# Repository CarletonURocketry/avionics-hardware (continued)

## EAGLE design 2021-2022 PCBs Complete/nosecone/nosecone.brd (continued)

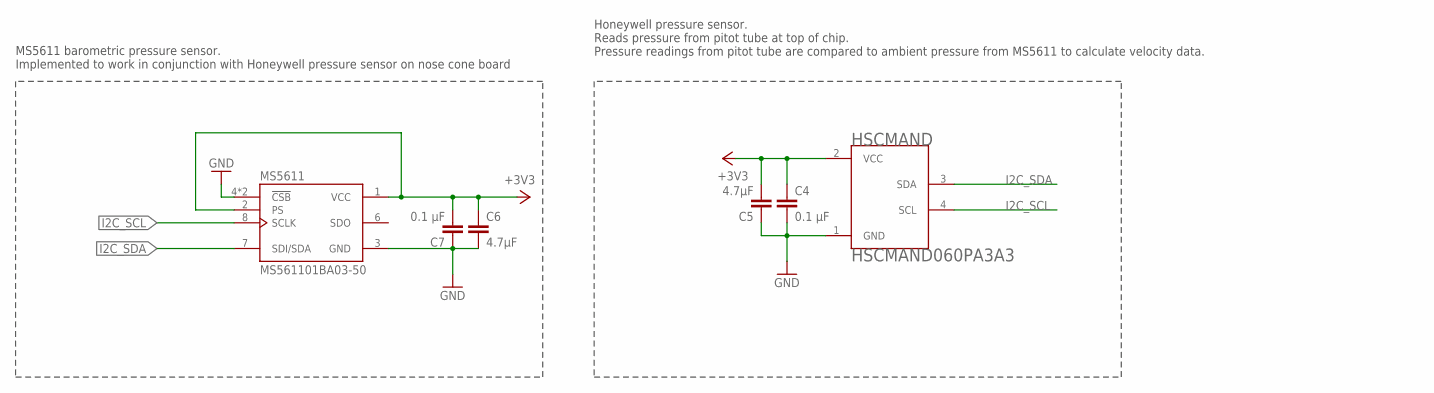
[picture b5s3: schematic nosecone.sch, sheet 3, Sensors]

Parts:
C4, C7: 0.1 µF; C0805
C5, C6: 4.7µF; C0805
HSCMAND: HSCMAND060PA3A3; HSC-SMT
MS5611: MS561101BA03-50; SON125P500X300X100-8N

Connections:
+3V3: C4.1, C5.2, C6.1, C7.2, HSCMAND.2 (VCC), MS5611.1 (VCC), MS5611.2 (PS); also elsewhere on the board
GND: C4.2, C5.1, C6.2, C7.1, HSCMAND.1 (GND), MS5611.3 (GND), MS5611.4 (!CSB), MS5611.5 (!CSB); also elsewhere on the board
I2C_SCL: HSCMAND.4 (SCL), MS5611.8 (SCLK); also elsewhere on the board
I2C_SDA: HSCMAND.3 (SDA), MS5611.7 (SDI/SDA); also elsewhere on the board

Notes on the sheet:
MS5611 barometric pressure sensor. Implemented to work in conjunction with Honeywell pressure sensor on nose cone board
Honeywell pressure sensor. Reads pressure from pitot tube at top of chip. Pressure readings from pitot tube are compared to ambient pressure from MS5611 to calculate velocity data.

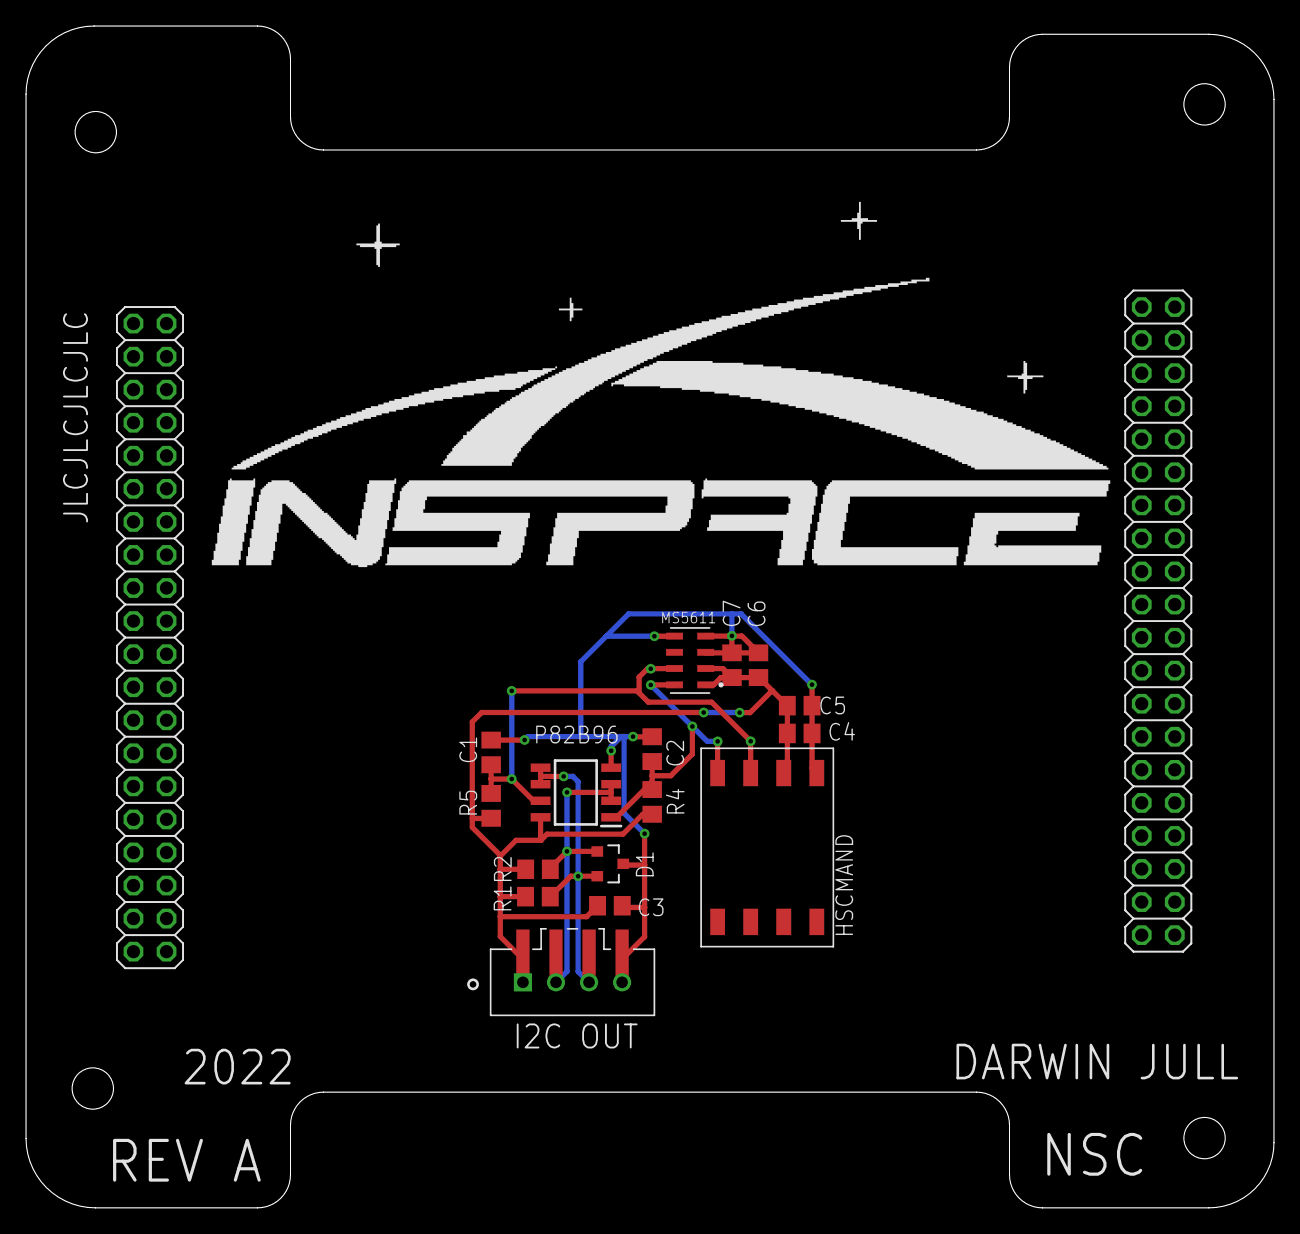
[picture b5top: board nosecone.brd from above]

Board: 2 copper layers, 95.9 x 90.8 mm, 19 parts (0 on the bottom side), 8 nets.

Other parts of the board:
U$2: INSPACE_7CM

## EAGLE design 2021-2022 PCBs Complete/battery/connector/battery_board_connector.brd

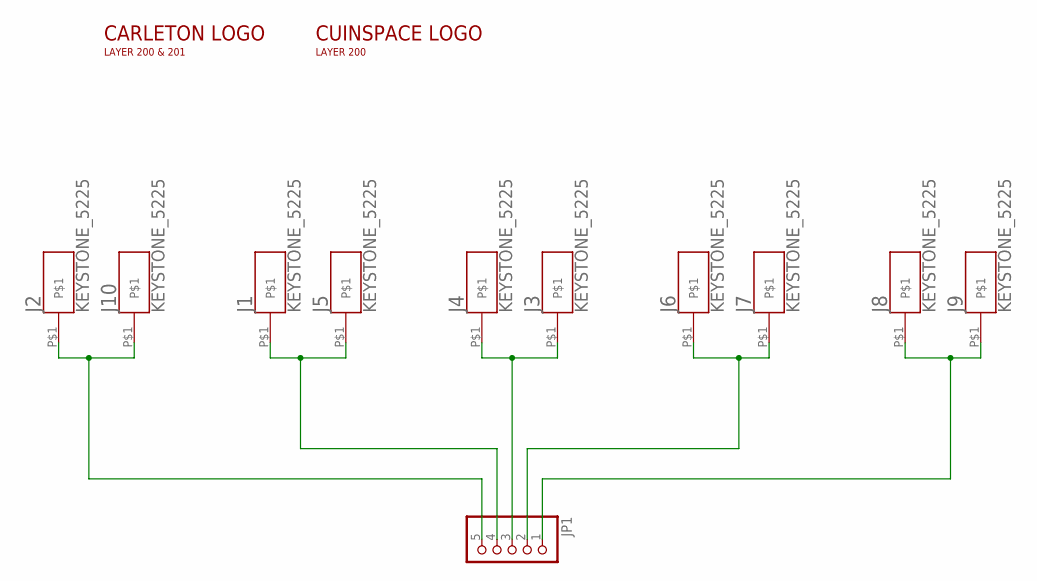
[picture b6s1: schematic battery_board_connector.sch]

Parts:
J1, J2, J3, J4, J5, J6, J7, J8, J9, J10: KEYSTONE_5225
JP1: PINHD-1X5; 1X05
U$1: INSPACE3CM; INSPACE_3CM
U$2: CARLETON3CM; CARLETONU_3CM

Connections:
unnamed: J2.P$1, J10.P$1, JP1.5
unnamed: J1.P$1, J5.P$1, JP1.4
unnamed: J3.P$1, J4.P$1, JP1.3
unnamed: J6.P$1, J7.P$1, JP1.2
unnamed: J8.P$1, J9.P$1, JP1.1

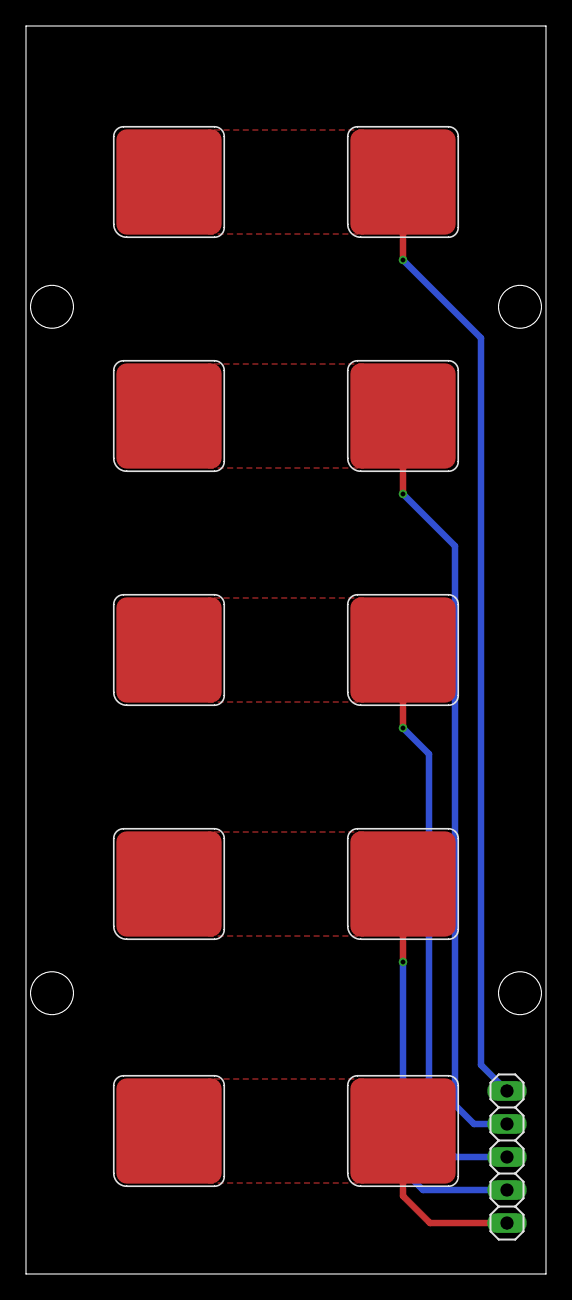
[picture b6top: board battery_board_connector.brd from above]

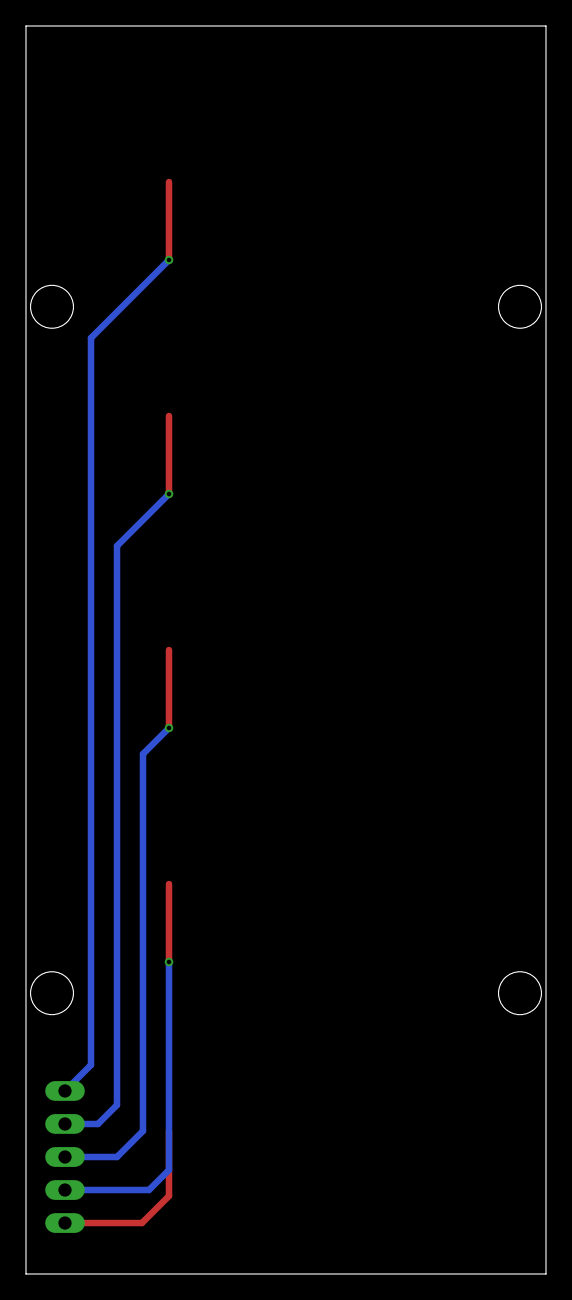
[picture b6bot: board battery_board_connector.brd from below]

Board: 2 copper layers, 40.0 x 96.0 mm, 13 parts (2 on the bottom side), 5 nets.

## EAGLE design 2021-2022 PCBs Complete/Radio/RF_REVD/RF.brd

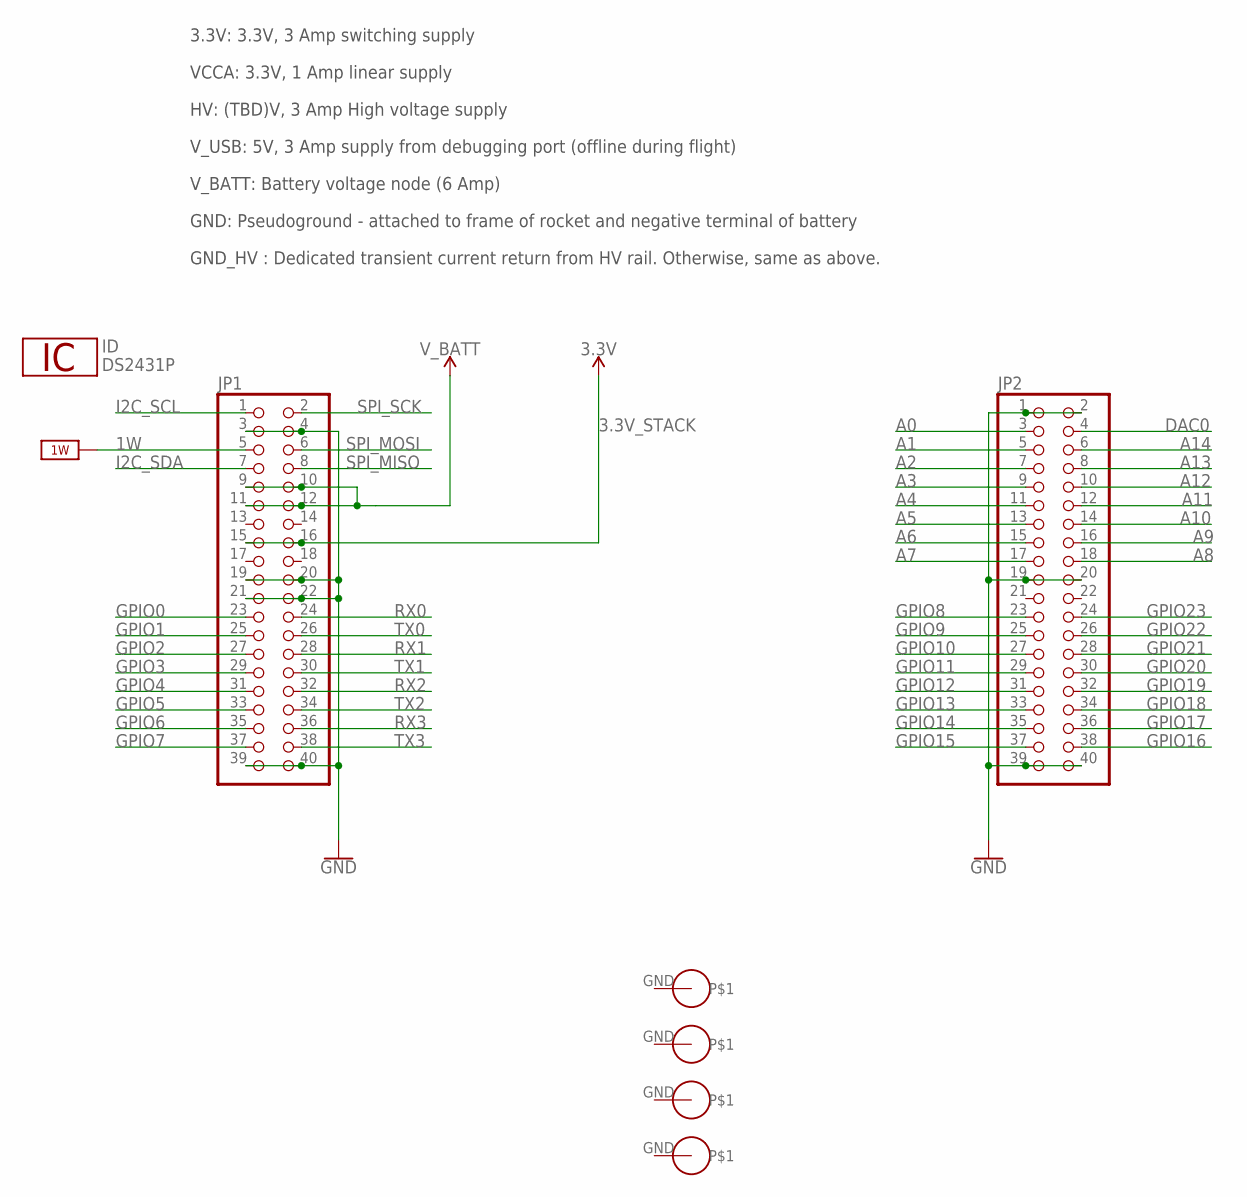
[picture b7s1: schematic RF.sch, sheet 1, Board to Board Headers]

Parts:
ID: DS2431P; TSOC6
JP1, JP2: PINHD-2X20; 2X20
U$1, U$2, U$3, U$4: PS/104-MOUNTING-HOLE; PC/104-MOUNTING-HOLE

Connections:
1W: ID.2 (1W), JP1.5
3.3V_STACK: JP1.15, JP1.16; also elsewhere on the board
A0: JP2.3
A1: JP2.5
A2: JP2.7
A3: JP2.9
A4: JP2.11
A5: JP2.13
A6: JP2.15
A7: JP2.17
A8: JP2.18
A9: JP2.16
A10: JP2.14
A11: JP2.12
A12: JP2.10
A13: JP2.8
A14: JP2.6
DAC0: JP2.4
GND: ID.1 (GND), JP1.3, JP1.4, JP1.19, JP1.20, JP1.21, JP1.22, JP1.39, JP1.40, JP2.1, JP2.2, JP2.19, JP2.20, JP2.39, JP2.40; also elsewhere on the board
GPIO0: JP1.23
GPIO1: JP1.25
GPIO2: JP1.27
GPIO3: JP1.29
GPIO4: JP1.31
GPIO5: JP1.33
GPIO6: JP1.35
GPIO7: JP1.37
GPIO8: JP2.23
GPIO9: JP2.25
GPIO10: JP2.27
GPIO11: JP2.29
GPIO12: JP2.31
GPIO13: JP2.33
GPIO14: JP2.35
GPIO15: JP2.37
GPIO16: JP2.38
GPIO17: JP2.36
GPIO18: JP2.34
GPIO19: JP2.32
GPIO20: JP2.30
GPIO21: JP2.28
GPIO22: JP2.26
GPIO23: JP2.24
I2C_SCL: JP1.1
I2C_SDA: JP1.7
unnamed: JP1.9, JP1.10, JP1.11, JP1.12
RX0: JP1.24; also elsewhere on the board
RX1: JP1.28; also elsewhere on the board
RX2: JP1.32; also elsewhere on the board
RX3: JP1.36
SPI_MISO: JP1.8
SPI_MOSI: JP1.6
SPI_SCK: JP1.2
TX0: JP1.26; also elsewhere on the board
TX1: JP1.30; also elsewhere on the board
TX2: JP1.34; also elsewhere on the board
TX3: JP1.38

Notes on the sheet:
VCCA: 3.3V, 1 Amp linear supply
HV: (TBD)V, 3 Amp High voltage supply
V_USB: 5V, 3 Amp supply from debugging port (offline during flight)
V_BATT: Battery voltage node (6 Amp)
3.3V: 3.3V, 3 Amp switching supply
GND: Pseudoground - attached to frame of rocket and negative terminal of battery
GND_HV : Dedicated transient current return from HV rail. Otherwise, same as above.

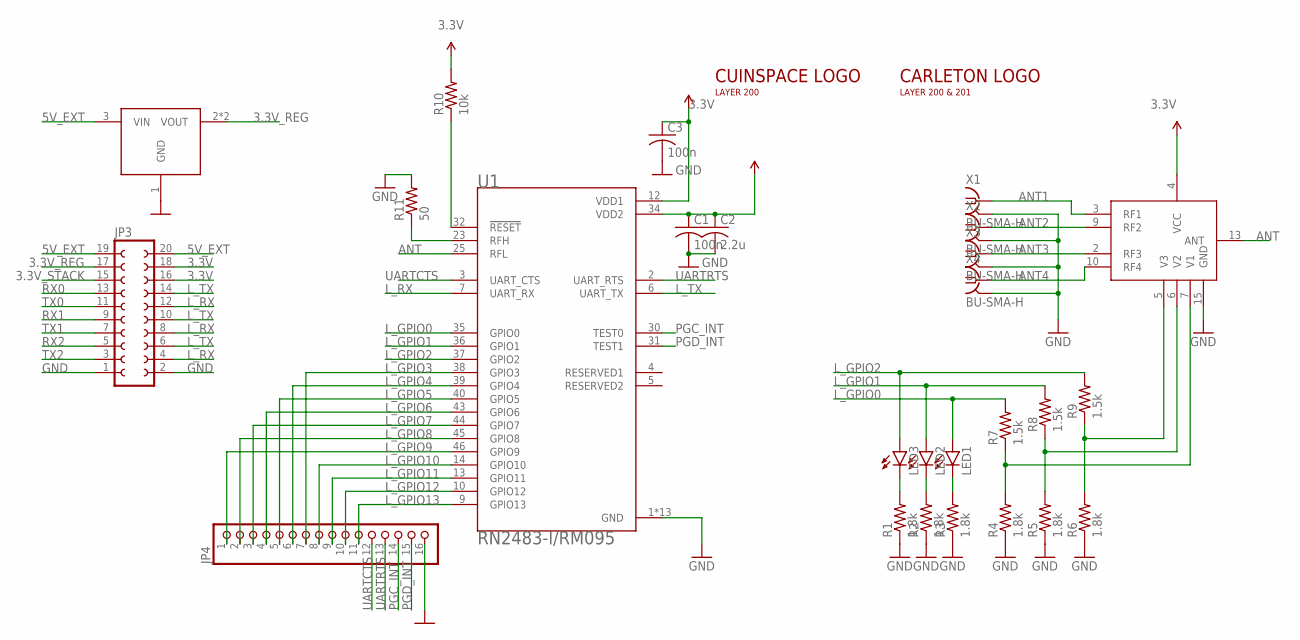
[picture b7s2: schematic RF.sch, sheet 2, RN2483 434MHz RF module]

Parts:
C1, C3: 100n; C0805
C2: 2.2u; C0805
JP3: FE10-2
JP4: PINHD-1X16; 1X16
LED1, LED2, LED3: LEDSMT1206; 1206
R1, R2, R3, R4, R5, R6: 1.8k; R0805
R7, R8, R9: 1.5k; R0805
R10: 10k; R0805
R11: 50; R0805
U1: RN2483-I/RM095; MICROCHIP_RN2483-I/RM095
U2: SKY13414; QFN45P200X200X55-15N
U3: LDL1117S33R; SOT223
U$6: INSPACE5CM_L; INSPACE_5CM_LETTERS
U$7: CARLETON3CM; CARLETONU_3CM
X1, X2, X3, X4: BU-SMA-H

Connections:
3.3V: C1.1, C2.1, C3.1, JP3.16, JP3.18, R10.2, U1.12 (VDD1), U1.34 (VDD2), U2.4 (VCC)
3.3V_REG: JP3.17, U3.2 (VOUT), U3.4 (VOUT)
3.3V_STACK: JP3.15; also elsewhere on the board
5V_EXT: JP3.19, JP3.20, U3.3 (VIN)
ANT: U1.25 (RFL), U2.13 (ANT)
ANT1: U2.3 (RF1), X1.1
ANT2: U2.9 (RF2), X2.1
ANT3: U2.2 (RF3), X3.1
ANT4: U2.10 (RF4), X4.1
GND: C1.2, C2.2, C3.2, JP3.1, JP3.2, JP4.16, R1.1, R2.1, R3.1, R4.1, R5.1, R6.1, R11.2, U1.1 (GND), U1.8 (GND), U1.11 (GND), U1.20 (GND), U1.21 (GND), U1.22 (GND), U1.24 (GND), U1.26 (GND), U1.27 (GND), U1.28 (GND), U1.33 (GND), U1.41 (GND), U1.47 (GND), U2.15 (GND), U3.1 (GND), X1.2, X1.3 (2), X1.4 (2), X1.5 (2), X2.2, X2.3 (2), X2.4 (2), X2.5 (2), X3.2, X3.3 (2), X3.4 (2), X3.5 (2), X4.2, X4.3 (2), X4.4 (2), X4.5 (2); also elsewhere on the board
L_GPIO0: LED1.A, R7.2, U1.35 (GPIO0)
L_GPIO1: LED2.A, R8.2, U1.36 (GPIO1)
L_GPIO2: LED3.A, R9.2, U1.37 (GPIO2)
L_GPIO3: JP4.7, U1.38 (GPIO3)
L_GPIO4: JP4.6, U1.39 (GPIO4)
L_GPIO5: JP4.5, U1.40 (GPIO5)
L_GPIO6: JP4.4, U1.43 (GPIO6)
L_GPIO7: JP4.3, U1.44 (GPIO7)
L_GPIO8: JP4.2, U1.45 (GPIO8)
L_GPIO9: JP4.1, U1.46 (GPIO9)
L_GPIO10: JP4.8, U1.14 (GPIO10)
L_GPIO11: JP4.9, U1.13 (GPIO11)
L_GPIO12: JP4.10, U1.10 (GPIO12)
L_GPIO13: JP4.11, U1.9 (GPIO13)
L_RX: JP3.4, JP3.8, JP3.12, U1.7 (UART_RX)
L_TX: JP3.6, JP3.10, JP3.14, U1.6 (UART_TX)
unnamed: R4.2, R7.1, U2.7 (V1)
unnamed: R5.2, R8.1, U2.6 (V2)
unnamed: R11.1, U1.23 (RFH)
unnamed: LED3.C, R1.2
unnamed: LED2.C, R2.2
unnamed: R6.2, R9.1, U2.5 (V3)
unnamed: R10.1, U1.32 (!RESET)
unnamed: LED1.C, R3.2
PGC_INT: JP4.14, U1.30 (TEST0)
PGD_INT: JP4.15, U1.31 (TEST1)
RX0: JP3.13; also elsewhere on the board
RX1: JP3.9; also elsewhere on the board
RX2: JP3.5; also elsewhere on the board
TX0: JP3.11; also elsewhere on the board
TX1: JP3.7; also elsewhere on the board
TX2: JP3.3; also elsewhere on the board
UARTCTS: JP4.12, U1.3 (UART_CTS)
UARTRTS: JP4.13, U1.2 (UART_RTS)

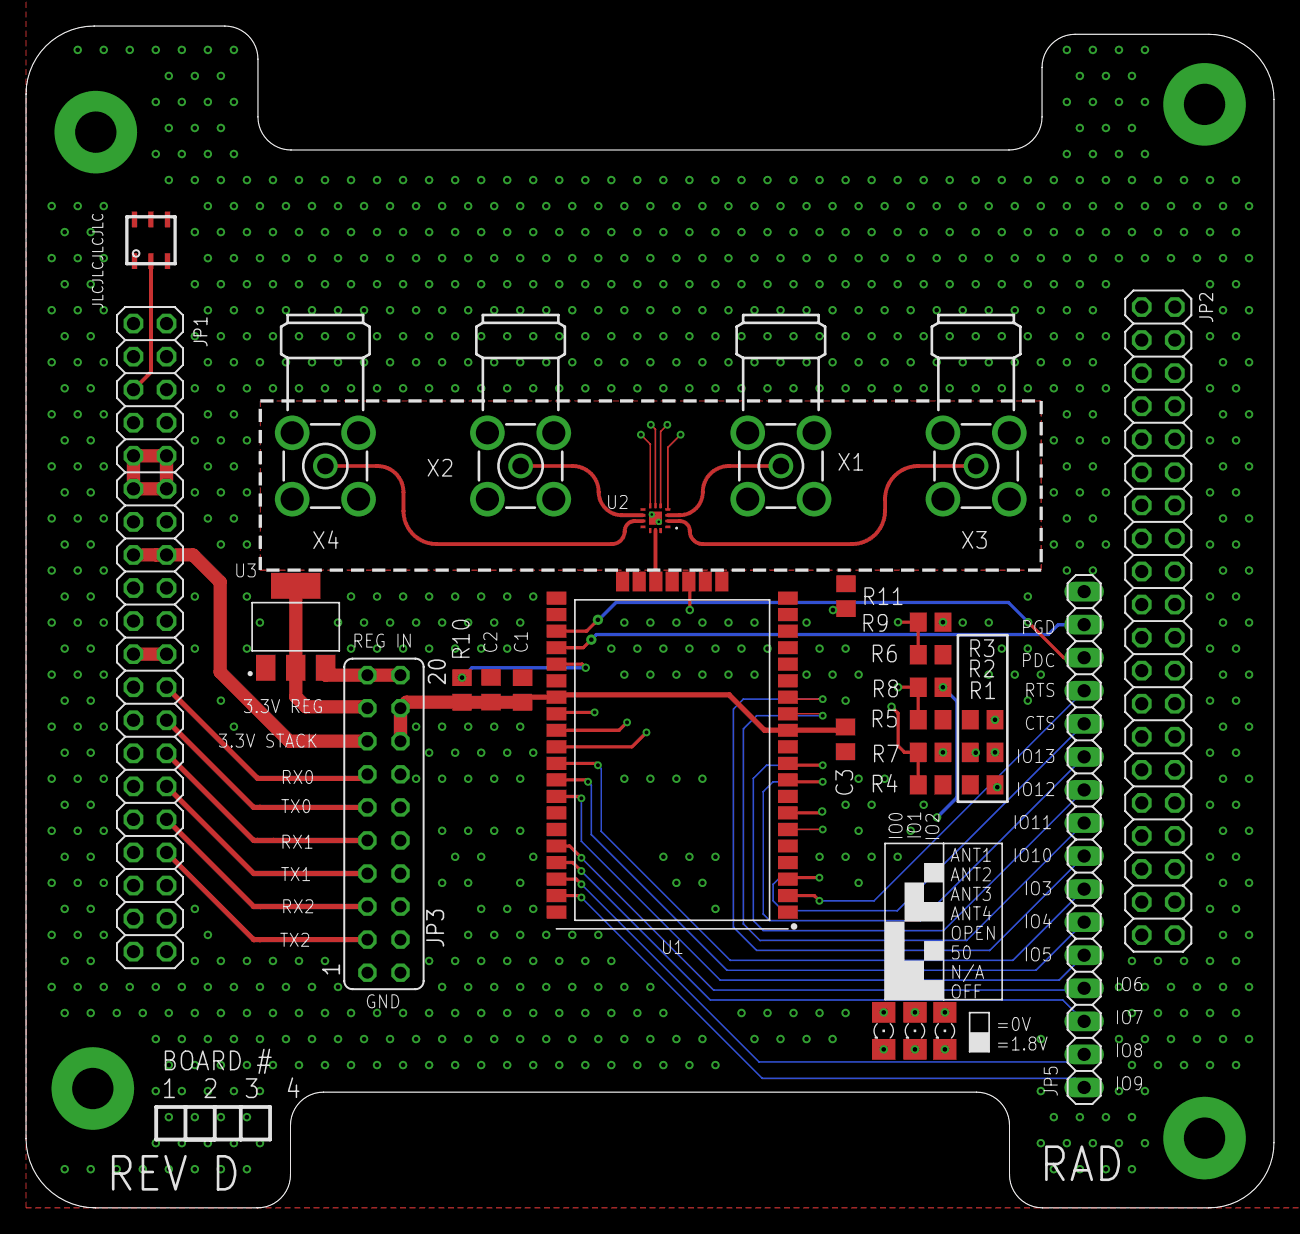
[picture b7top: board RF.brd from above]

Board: 4 copper layers, 95.9 x 90.8 mm, 35 parts (0 on the bottom side), 46 nets.

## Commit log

2019-11-09 Add .gitignore
2019-11-10 Moved PCB files into directories
2019-11-10 Remove original copies of boards
2021-03-17 Add Big MCU board rev. a
2021-09-02 Add Big MCU board
2021-09-02 Add antenna board
2021-09-08 asdf
2021-09-08 4 Layer PCB Template.
    Delete extra headers and layers as needed. Enjoy!
2021-09-08 New Logos!
2021-09-08 Create asdf
2021-09-08 New 2021 PCB Template
2021-09-08 Re-organize
2021-09-11 +Radio Board
2021-09-22 + PWR REVD
2021-09-22 + Design Blocks
2021-09-22 + RF Spacer
2021-09-23 + connector board
2021-09-23 Update Rev #
2021-09-24 + Deployment Board
2021-09-24 JLCJLCJLC
2021-09-26 Update antenna board
2021-09-26 Add battery sandwich boards
2022-06-16 End of Year Update
    Adding the boards that I have designed and built this year. Includes the following boards:
    -nosecone
    -payloaduplink
    -I2CBuff
    Also set up new folders for 2022-2023 schoolyear. Includes folder for new board template files (same template as 2021-2022) and folder for new boards designed in 2022-2023 schoolyear.
2022-07-31 Added WIP Boards, Pinout Schematic
2022-08-01 Added Backplane Board Schematic
2022-08-01 Created Backplane Board Shape
2022-08-02 Added Backplane Connector Pinout
2022-10-22 Redimensioned Backplane Board
    Changed Y dimension from 145.3mm to 146.8mm
2022-11-04 Created DEP_REVC.schdoc
    Created DEP_REVC schematic and associated files
2022-11-04 Create DEP_REVC_BOM.xlsx
    Added bill of materials
2022-11-04 Create datasheets
    Added datasheets for all primary IC's
2022-11-11 Updated Resistors
    Updated R5 to allow for identical eMatch current outputs
2022-11-12 Created GEN2 PCB Template
    Board shape has been defined, pending final checks on dimensions before use in current designs. Currently missing card edge connector contacts
2022-11-12 Modified Backplane Dimensions
    Changed backplane dimensions to 146.80mmx99.50mm. Modified drill hole placement to match.
2022-11-13 Created LED Circuit, Selected LED
    KP DELPS1.FP-QISI-34-U515-2-S LED will be used and 200 ohm resistor
2022-11-13 Aligned and organized backplane components
    Corrected issue with net naming and duplicate nets. Correctly aligned and locked all components.
2022-11-13 Modified Design Rules, Began Routing
    Modified design rules to comply with JLCPCB manufacturing specs. Placed vias for routing connectors. Routed slot indicator LEDs
2022-11-13 Modified Pinout
    Completely changed pinout of avionics backplane. Moved digital connections to top of connector, analog and GPIO to bottom. There are now 3 power ports (2 +3.3V and 1 +5V)
2022-11-16 Vias Arranged
    Vias arranged before array paste
2022-11-17 Routed Backplane
    Backplane routing completed. Now requires silkscreen work and final checks
2022-11-17 Backplane routing completed (#14)
    * Vias Arranged
    Vias arranged before array paste
    * Routed Backplane
    Backplane routing completed. Now requires silkscreen work and final checks
2022-11-18 Create CU Logos
    Create Carleton University full logo and Carleton University Shield Logo
2022-11-18 Create FED-Logo.png
    Create Faculty of Engineering and Design Logo
2022-11-18 Create InSpace logos
    Create CU InSpace logo with border, logo, and text logo
2022-11-25 Created Project Files
2022-11-25 Added Connectors
2022-11-25 Added Connectors to Schematic
2022-11-25 Deleted Schematic Library
    Did not work as intended, model files were not included.
2022-11-25 Changed some footprints
    Changed footprints of AQY282EH to be SMT not through hole
2022-11-26 Created GEN2 Board Contacts
    Gen 2 Template board contacts have been completed. Final shape was decided (fit to exact connector dimensions). Exported design rules and nets from backplane
2022-11-28 Overwriting Old Files from BU
    Files were accidentally overwritten during merge. Updating with correct backplane files.
2022-11-28 Correcting overwritten files
    Uploading corrected files from backup
2022-12-04 Modified REVA of BCK and TEST for Manufacturing
    Changed TEST silkscreen.
    Created Gerber files for manufacturing by JLCPCB.
2022-12-05 Create DEP_REVC.pcbdoc
    Created and routed deployment board.
2022-12-05 Updated Board Dimensions
    Updated board dimensions to account for connector tolerances and JLCPCB tolerances.
2022-12-06 Modified corner size
    Interior board corners now at 45 degree angle
2022-12-06 Modified DEP_REVC.pcbdoc
    Adjusted PCB to meet new template requirements
2022-12-07 Updated PCB to follow battery polarity convention
2022-12-07 Fixed battery connector polarity
    updated battery connector connections to follow polarity convention
2022-12-07 Created CON_REVD
    Created and finished the battery & connector board
2022-12-07 Created Interface Board
    Created PCB to interface between GEN1 and GEN2 PCBs. Currently requires routing.
2022-12-07 Routed Interface Board
    Routing complete, still requires ground and power polygons + silkscreen and decals
2022-12-07 Final routing complete, decals added to INT PCB
    INT PCB now complete and ready for manufacturing. Output job files generated.
2022-12-07 Updated position of Conectors to reflect connector board
2022-12-07 Created DEP_REVC.intlib
2022-12-07 Update DEP_REVC.schdoc
    Added reverse polarity protection
2022-12-07 Added polarity protection
    Modified PCB routing to include polarity protection.
2022-12-08 Modified Routing
    Modified routing of DEP_REVC.pcbdoc to meet design requirements
2022-12-08 Removed temporary line
    Removed temporary line from DEP_REVC.pcbdoc
2022-12-08 Added component identifiers
    Added identifiers to Schottky diodes at outputs
2022-12-08 Updated routing
    Updated Routing and changed AQY282EH to AQY280SX
2022-12-08 Power Board Schematic Finished
    Sketch of power board complete
2022-12-08 Added FED logo
    Added FED logo to underneath of board
2022-12-09 Added Pads
    Added Pads to allow more options for current limiting
2022-12-09 Changed Current Limiting Circuit
    Replaced LM317 linear regulator with resistor
2022-12-09 Optimized routing
2022-12-09 Finished PWR_REVE
    After a 4.5 hour design session the PCB is complete and ready to be ordered.
2022-12-09 Created GerberX2 files
    Created files for manufacturing
2023-01-27 Added3D models
    Added 3D models for EasyMini altimeter and featherweight GPS tracker
2023-01-27 Created COTS_REVB.pcbprj
    Created COT PCB and initial component placement
2023-01-30 Adjusted 3D Model
    Modified model for battery holder to allow for batteries on both sides on the board.
2023-01-31 Inital Routing
    Initial routing of COTS_REVB.pcbdoc
2023-01-31 Added Reverse Polarity Protection
    Added reverse polarity protection to EasyMini outputs
2023-01-31 Changed GPS Battrey Connector
    Modified board connector to GPS Battery Input
2023-02-02 Updated connectors and footprints
    Modified some connectors, minor layout changes, and footprint changes/verification.
2023-02-02 Updated Connector Pinout
    Modified Pinout of Connector J3
2023-02-02 Removed Designator
    Removed unintentional designator from Silkscreen
2023-02-07 Change COTS_REVB.schdoc
    Modified Schematic to be easier to understand
2023-02-08 Updated Some designators
2023-02-22 Added RevA ground station hardware schematics and files to the completed folder for 2021-2022.
2023-02-23 Set up Altium project with schematic and PCB.
2023-02-23 Renaming sheets
2023-02-23 Rename
2023-02-23 Resized PCB to 100mmx100mm specifications. Added the main parts from the Eagle schematics.
2023-02-23 Added a few more components to the UART connector.
2023-02-23 Added ports between RN2483 and the UART-USB. Finished UART-USB besides the debug header pin.
2023-02-23 Added debug header pins.
2023-02-23 Started on USB connection but the micro-usb connector from the Eagle design does not have an available Altium footprint.
2023-02-23 Added micro-usb connector
2023-02-24 Added pin headers for ICSP
2023-02-24 Added 4-pin header and comments from the original schematic.
2023-02-24 Added some more original comments.
2023-02-24 Added original comments and all parts except the antennas.
2023-02-24 added page number
2023-02-24 Annotated schematics.
2023-02-24 Refreshed PCB document and added BOM.
2023-03-01 Removed PCB
2023-03-01 Added SMA connectors.
2023-03-01 Removed RFH antenna connector because Darwin said so (rocket never transmits over high frequency.
2023-03-02 RFH gets tied to ground through a resistor (of a value idk) because Darwin said so.
2023-03-02 Shaped the PCB to be 100mmx100mm (the max limit)
2023-03-08 tjing
2023-03-08 Removed reset switch
2023-03-08 Shield pins are floating to prevent current flowing up from ground planes at different potentials.
2023-03-09 Removed debug header cause we can just probe the traces
2023-03-09 Cleaned up schematic appearance.
2023-03-09 Minor fix.
2023-03-09 More aesthetic changes.
2023-03-09 Specific resistors and capacitors!
2023-03-09 Added specific LEDs and a couple resistors I missed.
2023-03-09 Tied floating pins high because they are active low and were previously unused on RevA
2023-03-09 I put the things on the board! In a shitty way but it's better than the auto place.
2023-03-09 Moved some more things around the board
2023-03-14 Create Manufacturing Files
    Create Gerber files for manufacturing
2023-03-14 Updated project with GBR files
2023-03-15 Replicated the layout of REVA slightly
2023-03-18 Renamed GBR files
2023-03-22 Finished the nets!
2023-03-22 BOM added.
2023-03-22 Created RF_REVE Board
2023-03-22 Complete board overhaul and better connectors. Routing is still unfinished for USB to UART.
2023-03-23 Finished RF_REVE
2023-03-23 Changed traces and GPIO pins
2023-03-23 Updated Routing
    Minor cleanup of routing
2023-03-23 Updated silkscreen
    Updated pin names on J1 to reflect the pins on the main chip they are connected to
2023-03-23 Updated schematic
    Updated components on schematic to fix issues with 3D models
2023-03-24 Completed the routing. The traces between USB to UART could not be done witout vias and were done with vias in the REVA design. Routing is not as clean as the REVA design and should be reviewed by so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
2023-03-25 Changed Silks and Altered Voltage Pins
2023-03-28 Updated antenna trace impedence
    Updated antenna trace impedance, changed some net names
2023-03-29 Routed USB as differential pair
    Routed USB as differential pair with 90 ohm impedance. Updated schematic to use off sheet connecters and net labels instead of ports.
2023-03-29 Updated Silkscreen and designators
2023-03-30 Finished board
    Finished Routing
    Created Gerber files for manufacturing
2023-03-30 Create GND_REVB.step
    Created 3D model of board
2023-03-30 Saved project file
    Forgot to do with earlier commit
2023-03-30 Updated manufacturing files
2023-03-30 Updated board shape
    Added rounded corners
2023-03-30 Update GND_REVB.step
    Updated 3D model to include rounded corners
2023-03-30 Check Description
    Moved RF_REVE.pcbdoc from the templates folder to the correct location
    Generated Gerber files for manufacturing
2023-08-24 End of Year
    `End of Work on 2022-2023 Version. Switching to 2023-2024 version
2023-08-24 Created EasyMini_Connector.pcbprj
    Created PCB project and initial schematic for EasyMini Connector RevB
2023-08-25 Created Featherweight_Connector.pcbprj
    Created Featherweight_Connector.pcbprj and initial schematic
2023-10-22 Cots interfaces (#16)
    * Added3D models
    Added 3D models for EasyMini altimeter and featherweight GPS tracker
    * Created COTS_REVB.pcbprj
    Created COT PCB and initial component placement
    * Adjusted 3D Model
    Modified model for battery holder to allow for batteries on both sides on the board.
